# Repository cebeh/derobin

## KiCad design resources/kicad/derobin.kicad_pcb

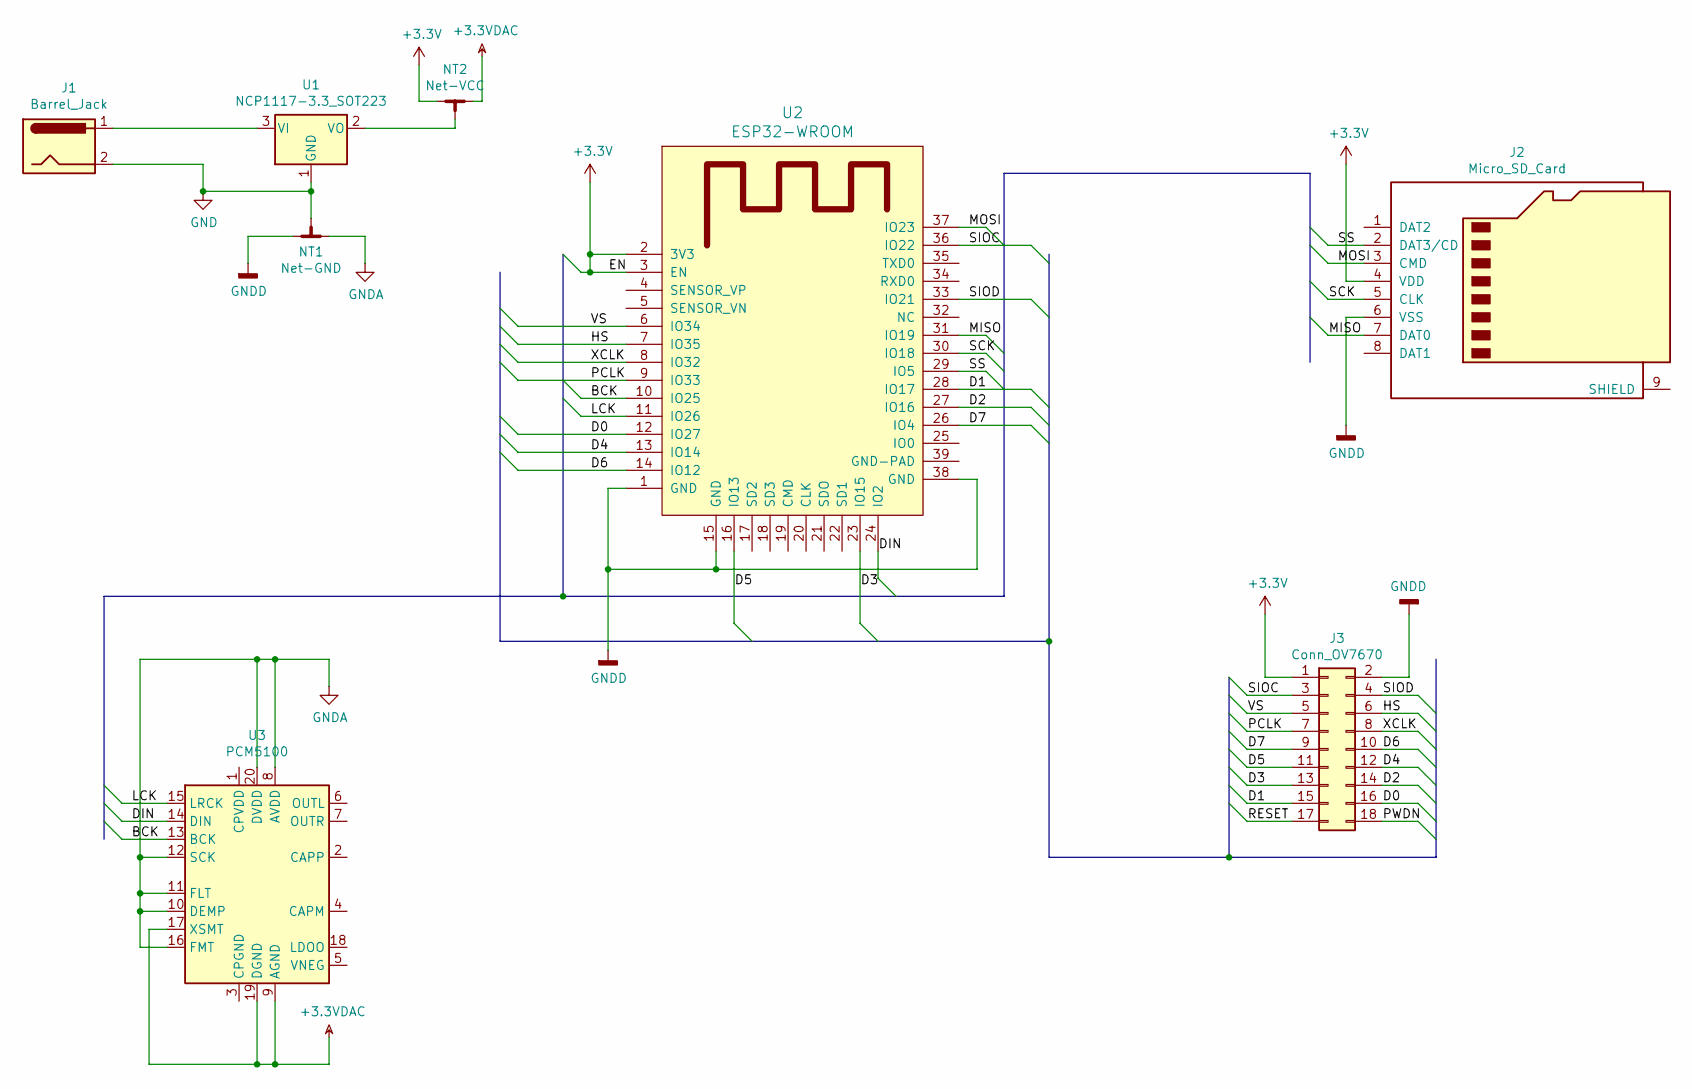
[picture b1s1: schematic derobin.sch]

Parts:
J1: Barrel_Jack; BarrelJack_CUI_PJ-102AH_Horizontal
J2: Micro_SD_Card; microSD_HC_Wuerth_693072010801
J3: Conn_OV7670; pin_array_9x2
NT1: Net-GND; NetTie-3_THT_Pad0.3mm
NT2: Net-VCC; NetTie-3_THT_Pad0.3mm
U1: NCP1117-3.3_SOT223; SOT-223-3_TabPin2
U2: ESP32-WROOM
U3: PCM5100; TSSOP-20_4.4x6.5mm_P0.65mm

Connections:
+3.3VDAC: NT2.2, U3.9 (AGND), U3.17 (XSMT), U3.19 (DGND)
+3V3: J2.4 (VDD), J3.1, NT2.1, U2.2 (3V3), U2.3 (EN)
/BCK: U2.10 (IO25), U3.13 (BCK)
/D0: J3.16, U2.12 (IO27)
/D1: J3.15, U2.28 (IO17)
/D2: J3.14, U2.27 (IO16)
/D3: J3.13, U2.23 (IO15)
/D4: J3.12, U2.13 (IO14)
/D5: J3.11, U2.16 (IO13)
/D6: J3.10, U2.14 (IO12)
/D7: J3.9, U2.26 (IO4)
/DIN: U2.24 (IO2), U3.14 (DIN)
/HS: J3.6, U2.7 (IO35)
/LCK: U2.11 (IO26), U3.15 (LRCK)
/MISO: J2.7 (DAT0), U2.31 (IO19)
/MOSI: J2.3 (CMD), U2.37 (IO23)
/PCLK: J3.7, U2.9 (IO33)
/PWDN: J3.18
/RESET: J3.17
/SCK: J2.5 (CLK), U2.30 (IO18)
/SIOC: J3.3, U2.36 (IO22)
/SIOD: J3.4, U2.33 (IO21)
/SS: J2.2 (DAT3/CD), U2.29 (IO5)
/VS: J3.5, U2.6 (IO34)
/XCLK: J3.8, U2.8 (IO32)
GND: J1.2, NT1.3, U1.1 (GND)
GNDA: NT1.1, U3.8 (AVDD), U3.10 (DEMP), U3.11 (FLT), U3.12 (SCK), U3.16 (FMT), U3.20 (DVDD)
GNDD: J2.6 (VSS), J3.2, NT1.2, U2.1 (GND), U2.15 (GND), U2.38 (GND)
unnamed: J1.1, U1.3 (VI)
unnamed: NT2.3, U1.2 (VO)

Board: 2 copper layers, 8 parts (0 on the bottom side), 28 nets, no tracks yet.

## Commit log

2018-11-13 main
2018-11-14 config
